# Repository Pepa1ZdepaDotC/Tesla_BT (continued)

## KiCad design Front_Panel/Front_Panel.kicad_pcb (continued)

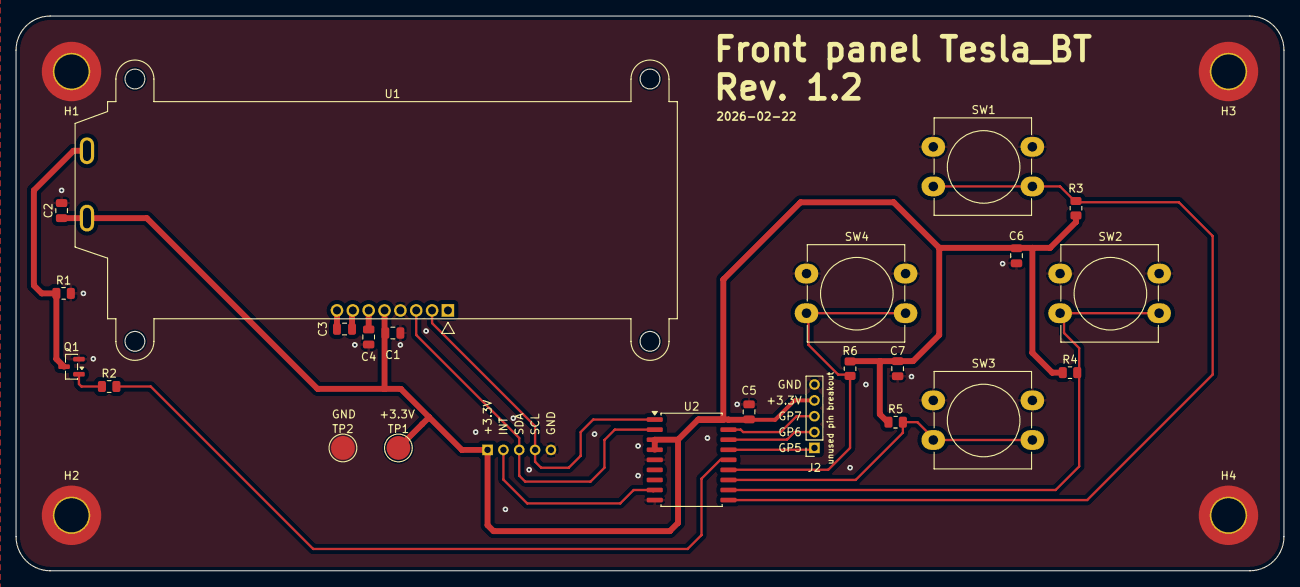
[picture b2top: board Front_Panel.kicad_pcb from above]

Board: 2 copper layers, 160.0 x 70.0 mm, 28 parts (1 on the bottom side), 18 nets.

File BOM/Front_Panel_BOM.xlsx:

Reference | Qty | Value | DNP | Exclude from BOM | Exclude from Board | Footprint | Datasheet
C1,C2,C3,C4 | 4 | 470nF |  |  |  | Capacitor_SMD:C_0805_2012Metric | ~
C5,C6,C7 | 3 | 100nF |  |  |  | Capacitor_SMD:C_0805_2012Metric | ~
H1,H2,H3,H4 | 4 | MountingHole_Pad |  | Excluded from BOM |  | MountingHole:MountingHole_4.3mm_M4_DIN965_Pad_TopBottom | ~
J1 | 1 | Conn_01x05 |  |  |  | Connector_PinSocket_2.00mm:PinSocket_1x05_P2.00mm_Vertical | ~
J2 | 1 | Conn_01x05 | DNP |  |  | Connector_PinSocket_2.00mm:PinSocket_1x05_P2.00mm_Vertical | ~
Q1 | 1 | BC817 |  |  |  | Package_TO_SOT_SMD:SOT-23 | https://www.onsemi.com/pub/Collateral/BC818-D.pdf
R1 | 1 | 0R | DNP |  |  | Resistor_SMD:R_0805_2012Metric | ~
R2 | 1 | 1K |  |  |  | Resistor_SMD:R_0805_2012Metric | ~
R3,R4,R5,R6 | 4 | 10K |  |  |  | Resistor_SMD:R_0805_2012Metric | ~
SW1,SW2,SW3,SW4 | 4 | SW_Push |  |  |  | Button_Switch_THT:SW_PUSH-12mm_Wuerth-430476085716 | ~
TP1,TP2 | 2 | TestPoint |  |  |  | TestPoint:TestPoint_Pad_D3.0mm | ~
U1 | 1 | NHD-C0220BIZ |  |  |  | Display:NHD-C0220BiZ | http://www.newhavendisplay.com/specs/NHD-C0220BiZ-FSW-FBW-3V3M.pdf
U2 | 1 | MCP23008-xSO |  |  |  | Package_SO:SOIC-18W_7.5x11.6mm_P1.27mm | http://ww1.microchip.com/downloads/en/DeviceDoc/MCP23008-MCP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

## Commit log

2025-11-29 updated pdf to match current schematic
2025-11-30 Netclasses, part Nums, LPF adjust
2025-11-30 Updated goals
2025-11-30 Update link text for schematic in README
2025-12-04 Edit readme
    Removed goals section from README.
2026-02-22 changes with BOM, minor fixes
2026-03-13 added step files
2026-03-14 Board ready for manufacturing, no more changes to either KiCad projects
2026-03-14 Added interactive BOM link
2026-05-17 Final Project Commit
